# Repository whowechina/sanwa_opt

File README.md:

# Optical sensor mod for Sanwa buttons (such as buttons for Pop'n Music, SDVX or IIDX) 

<video src="https://user-images.githubusercontent.com/11623830/221199948-686cd2df-5dc8-4df0-8924-246d5ef216d3.MP4" controls="controls" width="50%">
</video>

Traditional Sanwa buttons used in arcade use micro switches which wear out through time.
This project creates a optical sensor module that can replace the whole original lamp/switch holder and the microswitch. It almost never wears out.

I build it originally for my Pop'n Music controller, the Sanwa OBSA-100UMP button. And it turned out Sanwa has its own standard and my design works for many other Sanwa buttons such as SDVX and IIDX.

## PCB
The PCB contains the optical sensor part and the LED lamp part, you need to cut the lamp part from the main board.

For the optical sensor, the PCB supports both ITR1203 (inner pins) and discrete IR908-7C and PT908-7C pair (the outer pins). If you use discreate IR pairs, note that the IR emitter IR908-7C should be at the "U1" sign side, PT908-7C phototransistor should be at the opposite side.

* R1 is the current limiter for the emitter, 1206, 220 to 500ohm, depending on supply voltage. See notes below for calculation.
* R2 is for pulling down the out level, 1206 or 0805, 2K to 3K ohm, make sure the out level is high enough when button is not pressed (optical switch is on), if it's not high enough, increase R2 value.
* R3 is the current limiter for the LED lamp, depending on the brightness of the LED, 1206, 50ohm to 200ohm is fine.
* For the LED, choose 2835 or 3528 3V high brightness LEDs.

Notes:
* Here's how you can calculate the LED current limiter R3:
  * R3 = (V_supply - V_F) / I
  * LED V_F is usually around 3V. LED's current is usually 20mA for high brightness LEDs.
  * So R3 = (5V - 3V) / 0.02A = 100 ohm for a 5V supply.
* Same formular for the IR emitter current:
  * I = (V_supply - Vf_IR) / R1
  * IR emitter Vf is usually around 1.2V. IR emitter's current is usually 10 to 20mA.
  * So R1 = (5V - 1.2V) / 0.02A = 190 ohm, you can use a standard 220 ohm resistor.

## Holder
You need to print out the holder.stl. A resin printer is perfect for this. I'm not sure if an FDM printer with PLA has enough accuracy to do the work.

## Installation
1. Solder the lamp part onto the main board.
2. Use M1.8*8 screws to fix the board onto the holder.
3. Remove old lamp/switch holder from the button.
4. Push this new optical sensor back into the button.

## Sorry for the ZHR-5 interface
The interface to the mainboard is a ZHR-5, which is compatible with Sanwa's own buttons with optical sensors. I haven't made other types of interfaces yet. Maybe I will in the future.

* Good Luck! *

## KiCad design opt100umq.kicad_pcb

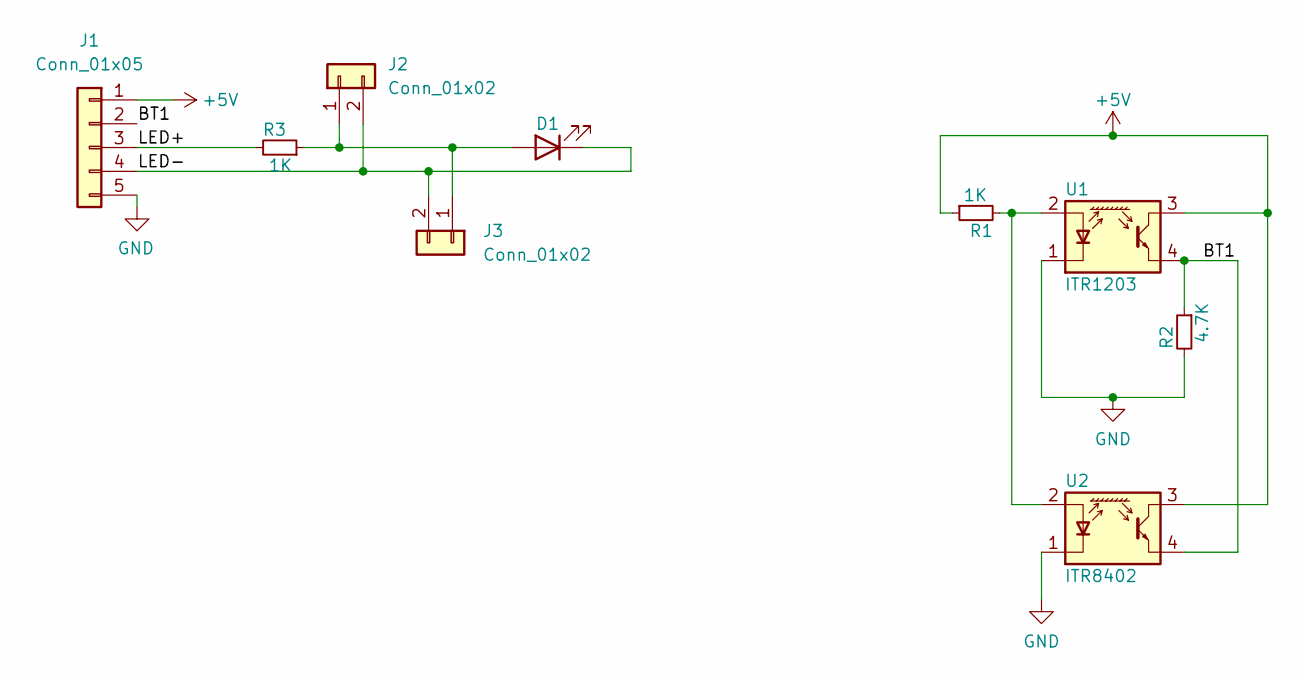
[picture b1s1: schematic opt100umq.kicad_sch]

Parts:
D1: IR26-21C_L110_TR8; LED3528_SIDE
J1: Conn_01x05; ZHR-5
J2: Conn_01x02; SIDE_CONTACT_A
J3: Conn_01x02; SIDE_CONTACT_B
R1, R3: 1K; R_1206_3216Metric; LCSC C22962
R2: 4.7K; R_1206_3216Metric; LCSC C22962
U1: ITR1203
U2: ITR8402

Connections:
+5V: J1.1, R1.1, U1.3, U2.3
/BT1: J1.2, R2.1, U1.4, U2.4
/LED+: J1.3, R3.2
/LED-: D1.1 (K), J1.4, J2.2, J3.2
GND: J1.5, R2.2, U1.1 (K), U2.1 (K)
unnamed: D1.2 (A), J2.1, J3.1, R3.1
unnamed: R1.2, U1.2 (A), U2.2 (A)

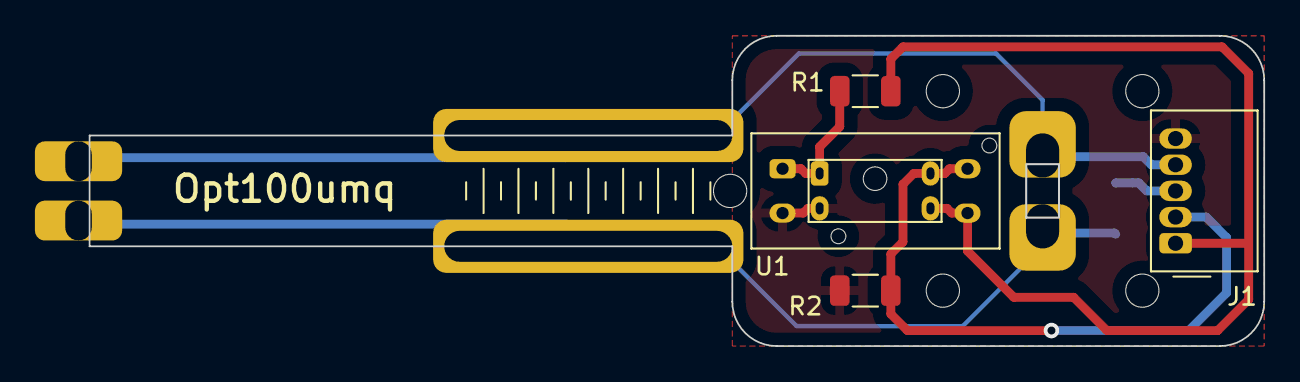
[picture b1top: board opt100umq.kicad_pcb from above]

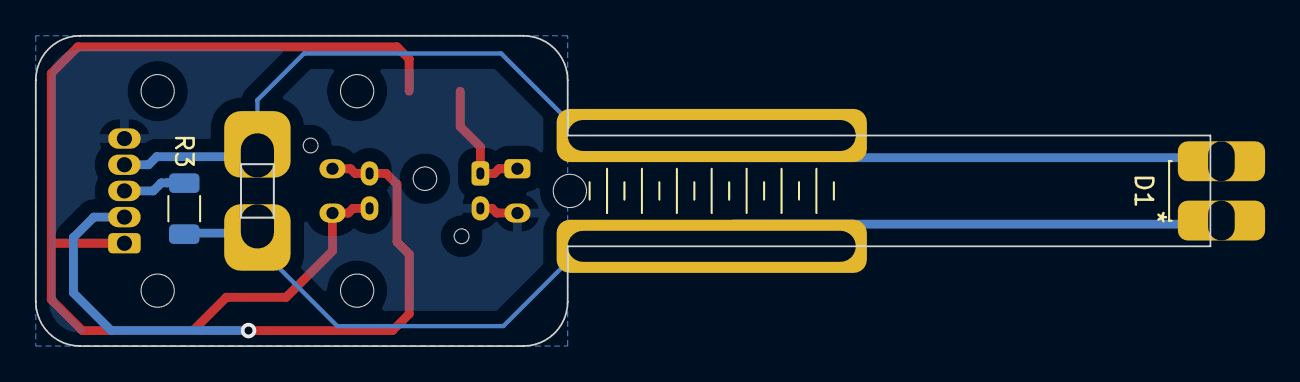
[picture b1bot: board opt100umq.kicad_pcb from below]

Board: 2 copper layers, 67.3 x 17.8 mm, 9 parts (2 on the bottom side), 7 nets.

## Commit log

2023-02-24 Migrated from misc
2023-02-24 Upload the demo video
2023-02-24 Update readme title
2023-02-24 Holder supports both optical sensor types
2025-12-25 IR options and resistor values
